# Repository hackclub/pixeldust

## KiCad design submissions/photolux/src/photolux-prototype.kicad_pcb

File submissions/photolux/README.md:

# photolux
created by: Gabriel Tsui [gbtsui] (slack id: U082VP0QX46)

[wokwi](https://wokwi.com/projects/428224523908486145)

I made a simple audio visualizer that takes input from a mono audio jack and flashes colors. It's pretty cool!

## BOM
<!-- Example: -->

| Comment               | Footprint                                               | Quantity | LCSC     | Cost     |
|------------------------|---------------------------------------------------------|----------|----------|----------|
| 100K resistor          | R_0805_2012Metric_Pad1.20x1.40mm_HandSolder              | 2        | C96346   |          |
| Surface mounted Neopixel | LED_SK6812MINI_PLCC4_3.5x3.5mm_P1.75mm                  | 12       |          |          |
| 4.7nF cap              | C_0805_2012Metric_Pad1.18x1.45mm_HandSolder              | 4        | C98192   |          |
| XIAO-RP2040-DIP        | XIAO-RP2040-DIP                                          | 1        |          |          |
| 100uF cap              | C_0805_2012Metric_Pad1.18x1.45mm_HandSolder              | 2        | C141660  |          |
| STX-3000 Audio Jack    | Jack_3.5mm_CUI_SJ-3523-SMT_Horizontal                    | 1        |          |          |
| 10K resistor           | R_0805_2012Metric_Pad1.20x1.40mm_HandSolder              | 2        | C84376   |          |
| 100Ω resistor          | R_0805_2012Metric_Pad1.20x1.40mm_HandSolder              | 1        | C105577  |          |
| 1uF decoupling cap     | C_0805_2012Metric_Pad1.18x1.45mm_HandSolder              | 1        | C28323   |          |
| Surge Protection Chip  | SOT-665                                                 | 1        | C552518  |          |
| 1.5nF cap              | C_0805_2012Metric_Pad1.18x1.45mm_HandSolder              | 1        | C541572  |          |

Design was honestly really hard. Originally I wanted to do baremetal but then i realized how difficult that would be to route and debug. So eventually I switched to my current design and finished it in like 5 hours. I then proceeded to forget about this for 3 weeks before submitting it properly.

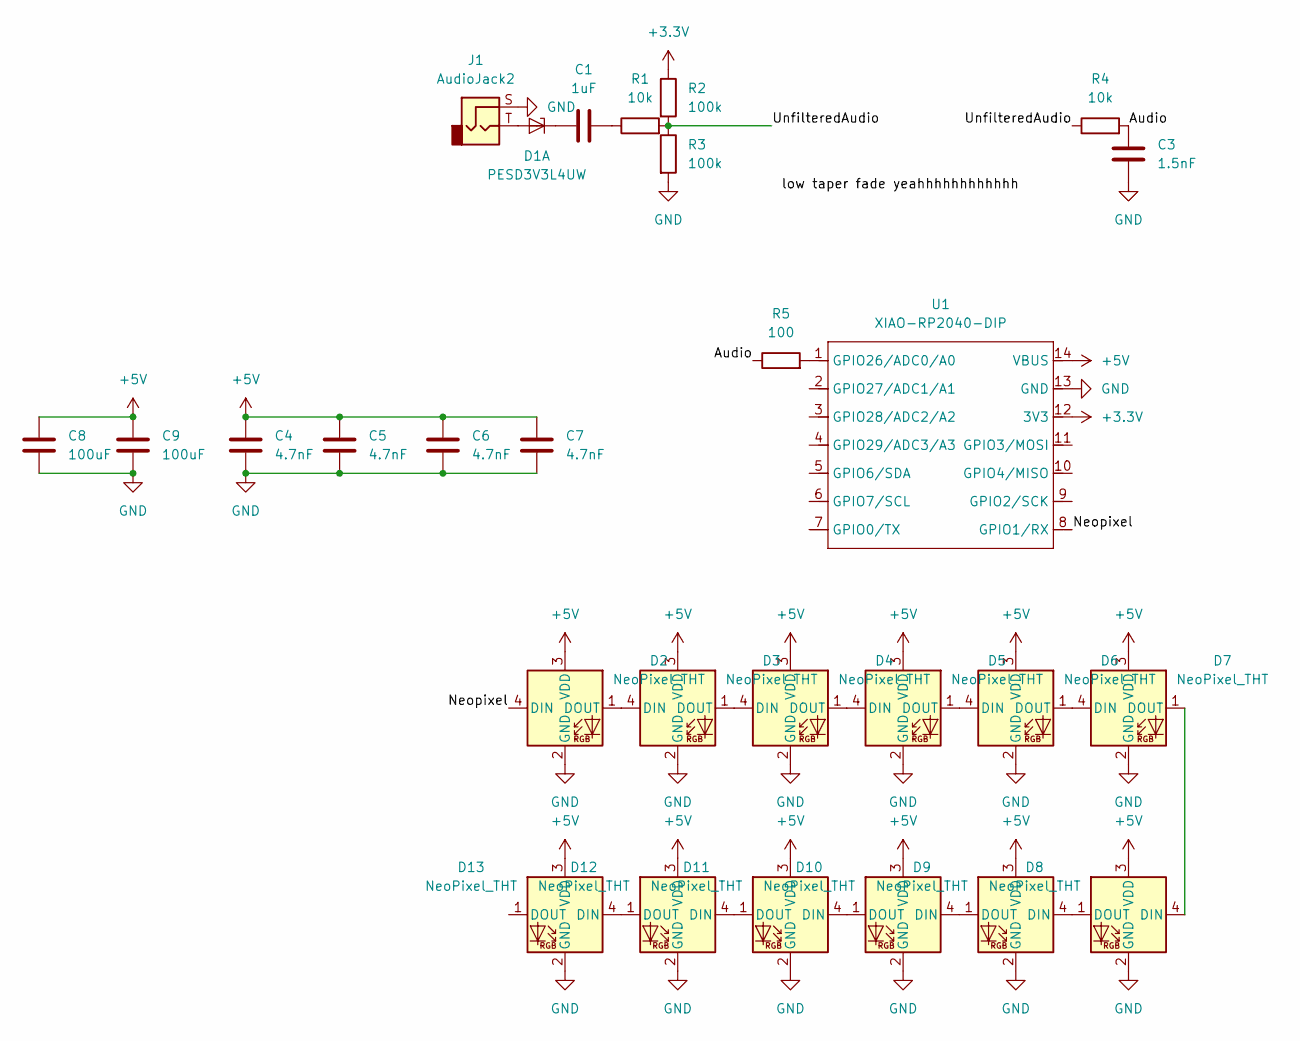
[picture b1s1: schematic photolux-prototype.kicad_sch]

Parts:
C1: 1uF; C_0805_2012Metric_Pad1.18x1.45mm_HandSolder
C3: 1.5nF; C_0805_2012Metric_Pad1.18x1.45mm_HandSolder
C4, C5, C6, C7: 4.7nF; C_0805_2012Metric_Pad1.18x1.45mm_HandSolder
C8, C9: 100uF; C_0805_2012Metric_Pad1.18x1.45mm_HandSolder
D1: PESD3V3L4UW; SOT-665
D2, D3, D4, D5, D6, D7, D8, D9, D10, D11, D12, D13: NeoPixel_THT; LED_SK6812MINI_PLCC4_3.5x3.5mm_P1.75mm
J1: AudioJack2; Jack_3.5mm_CUI_SJ-3523-SMT_Horizontal
R1, R4: 10k; R_0805_2012Metric_Pad1.20x1.40mm_HandSolder
R2, R3: 100k; R_0805_2012Metric_Pad1.20x1.40mm_HandSolder
R5: 100; R_0805_2012Metric_Pad1.20x1.40mm_HandSolder
U1: XIAO-RP2040-DIP

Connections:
+3.3V: R2.1, U1.12 (3V3)
+5V: C4.1, C5.1, C6.1, C7.1, C8.1, C9.1, D2.3 (VDD), D3.3 (VDD), D4.3 (VDD), D5.3 (VDD), D6.3 (VDD), D7.3 (VDD), D8.3 (VDD), D9.3 (VDD), D10.3 (VDD), D11.3 (VDD), D12.3 (VDD), D13.3 (VDD), U1.14 (VBUS)
/Audio: C3.1, R4.2, R5.1
/Neopixel: D2.4 (DIN), U1.8 (GPIO1/RX)
/UnfilteredAudio: R1.2, R2.2, R3.1, R4.1
GND: C3.2, C4.2, C5.2, C6.2, C7.2, C8.2, C9.2, D2.2 (GND), D3.2 (GND), D4.2 (GND), D5.2 (GND), D6.2 (GND), D7.2 (GND), D8.2 (GND), D9.2 (GND), D10.2 (GND), D11.2 (GND), D12.2 (GND), D13.2 (GND), J1.S, R3.2, U1.13 (GND)
unnamed: C1.2, R1.1
unnamed: D1.2 (A), J1.T
unnamed: C1.1, D1.1 (K1)
unnamed: D2.1 (DOUT), D3.4 (DIN)
unnamed: D3.1 (DOUT), D4.4 (DIN)
unnamed: D4.1 (DOUT), D5.4 (DIN)
unnamed: D5.1 (DOUT), D6.4 (DIN)
unnamed: D6.1 (DOUT), D7.4 (DIN)
unnamed: D7.1 (DOUT), D8.4 (DIN)
unnamed: D8.1 (DOUT), D9.4 (DIN)
unnamed: D9.1 (DOUT), D10.4 (DIN)
unnamed: D10.1 (DOUT), D11.4 (DIN)
unnamed: D11.1 (DOUT), D12.4 (DIN)
unnamed: D12.1 (DOUT), D13.4 (DIN)
unnamed: R5.2, U1.1 (GPIO26/ADC0/A0)

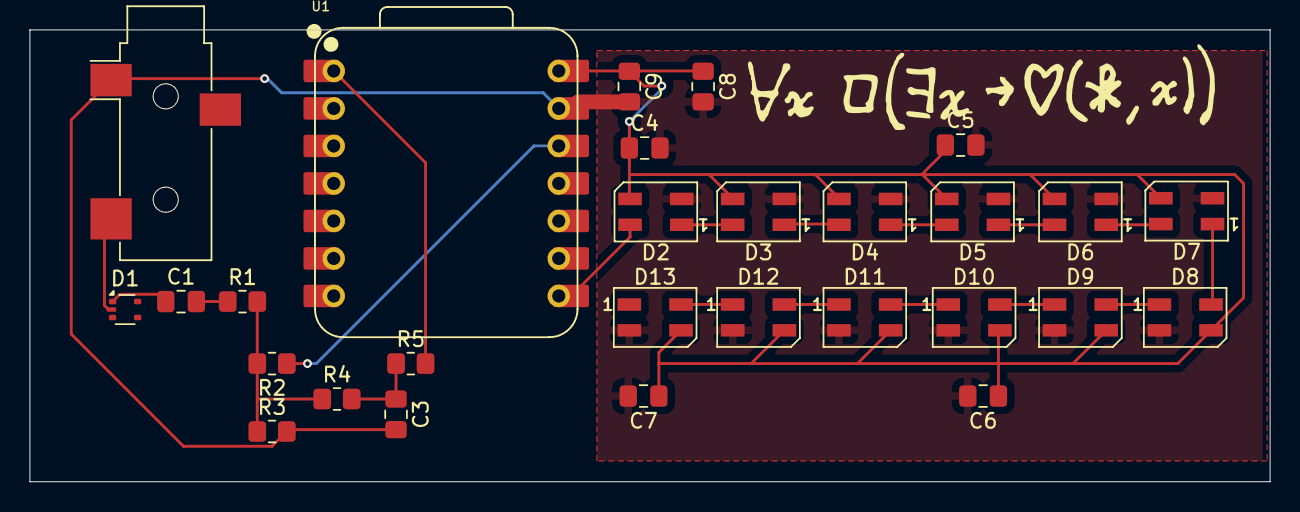
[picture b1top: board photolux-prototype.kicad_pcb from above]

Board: 2 copper layers, 84.0 x 30.6 mm, 28 parts (0 on the bottom side), 21 nets.

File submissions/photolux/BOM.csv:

Id;Designator;Footprint;Quantity;Designation;LCSC;Comments
1;R2,R3;R_0805_2012Metric_Pad1.20x1.40mm_HandSolder;2;100k;C96346;100K resistor
2;D6,D10,D7,D8,D11,D9,D13,D2,D5,D4,D3,D12;LED_SK6812MINI_PLCC4_3.5x3.5mm_P1.75mm;12;NeoPixel_THT;Surface mounted Neopixel;
3;C5,C6,C7,C4;C_0805_2012Metric_Pad1.18x1.45mm_HandSolder;4;4.7nF;C98192;4.7nF cap
4;U1;XIAO-RP2040-DIP;1;XIAO-RP2040-DIP;;
5;C9,C8;C_0805_2012Metric_Pad1.18x1.45mm_HandSolder;2;100uF;C141660;100uF cap
6;J1;Jack_3.5mm_CUI_SJ-3523-SMT_Horizontal;1;AudioJack2;;STX-3000 Audio Jack
7;R4,R1;R_0805_2012Metric_Pad1.20x1.40mm_HandSolder;2;10k;C84376;10K resistor
8;R5;R_0805_2012Metric_Pad1.20x1.40mm_HandSolder;1;100;C105577;100Ohm Resistor
9;C1;C_0805_2012Metric_Pad1.18x1.45mm_HandSolder;1;1uF;C28323;Decoupling Cap
10;D1;SOT-665;1;PESD3V3L4UW;C552518;Surge Protection Chip
11;C3;C_0805_2012Metric_Pad1.18x1.45mm_HandSolder;1;1.5nF;C541572;

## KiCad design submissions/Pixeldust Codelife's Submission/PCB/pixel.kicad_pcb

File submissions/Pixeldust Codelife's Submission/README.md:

name: "Delroy Prithvi Crasto"

slack_id: "U07V5RDRSL8"

github_handle: "@Programer6"

tutorial: [https://pixeldust.hackclub.com/guidelines](https://pixeldust.hackclub.com/guidelines)

wokwi: [https://wokwi.com/projects/430030406209979393](https://wokwi.com/projects/430030406209979393)  

# 10 * 10 Audio visualizer 

Wokwi link: [https://wokwi.com/projects/430030406209979393](https://wokwi.com/projects/430030406209979393)

I would like to solder the PCB myself (as 100 leds in total) and I don't have soldering iron, so I would like to have one.

Describe your board in 2-3 sentences. What are you making? What will it do? 
This board is an audio-reactive LED matrix: a 10x10 array of WS2812B LEDs controlled by an XIAO ESP32-S3. It listens to audio using an ICS-43434 microphone, processes the audio signal with the ESP32-S3, and applies the results to generate light animations on the LED matrix that are dynamically reactive to the audio to produce an eye-grabbing experience. A push button provides a method of user input.

Schematic and PCB images:

A simplified BOM table

| Component                      | Designator(s) | Footprint                                        | Quantity | LCSC Part # | Cost (USD)                           | Notes                                 |
| ------------------------------ | ------------- | ------------------------------------------------ | -------- | ----------- | ------------------------------------ | ------------------------------------- |
| WS2812B LED                    | D1–D100       | SMD5050 (5.0 × 5.0 mm)                           | 100      | C114586     | \$0.0651 each ([LCSC][1], [LCSC][2]) | 50+ price tier; 100 pcs order         |
| XIAO ESP32‑S3                  | U2            | test\:XIAO-ESP32S3-DIP                           | 1        | C20467913   | \$8.2231 ([LCSC][3])                 | 1 pc price                            |
| ICS‑43434 Microphone           | MK1           | Sensor\_Audio\:InvenSense\_ICS-43434‑6\_3.5x2.65 | 1        | —           | \$3.12 each ([DigiKey][4])           | DigiKey pricing for 1 pc              |
| 0.1 µF Capacitor (0603)        | C2            | C\_0603\_1608Metric                              | 1        | C6136995    | \$0.034 ([LCSC][5])                  | Venkel X7R MLCC, 25 V                 |
| 10 kΩ Resistor (0603)          | R1–R3         | R\_0603\_1608Metric                              | 3        | C2889392    | — (not in stock) ([LCSC][6])         | VO 100 mW thick‑film; no price listed |
| Push Button (Cherry MX)        | SW1           | SW\_Cherry\_MX\_1.00u\_PCB                       | 1        | C5687012    | \$1.632 ([LCSC][7])                  | 1+ price tier; out of stock           |
| AMS1117‑3.3 V Regulator        | U1            | SOT‑223‑3                                        | 1        | C6186       | \$0.183 ([LCSC][8])                  | 5+ price tier                         |
| 1000 µF Electrolytic Capacitor | C1            | SMD, D = 10 mm × L = 10.2 mm                     | 1        | C3359       | \$0.1061 ([LCSC][9])                 | Honor Elec, 16 V,  ±20%               |
| 1×3 Pin Header, Vertical       | J1, J2        | PinHeader\_1x03\_P2.54mm\_Vertical               | 2        | C5116482    | \$0.0239 each ([LCSC][10])           | ZHOURI 2.54‑1\*3, 3 pins              |
| Barrel Jack (Würth)            | J3            | Barrel\_Jack\_Switch\_Pin3Ring                   | 1        | —           | — (not on LCSC)                      | Part 694106301002; see Mouser/LCSC†   |
| SMD Indicator LED              | LED           | LED\_SMD\:Generic                                | 1        | —           | — (user‑defined)                     | Status indicator                      |

[1]: https://www.lcsc.com/product-detail/Light-Emitting-Diodes-LED_Worldsemi-WS2812B-B-W_C114586.html "WS2812B-B/W | Worldsemi | Price | In Stock | LCSC Electronics"
[2]: https://www.lcsc.com/product-detail/Light-Emitting-Diodes-LED_5050-RGBIntegrated-Light-4Pin_C114586.html "WS2812B-B/W | Worldsemi | Price | In Stock | LCSC Electronics"
[3]: https://www.lcsc.com/product-detail/Bluetooth-Modules_Seeed-113991114_C20467913.html "113991114 Seeed IoT/Communication Modules | Bluetooth ... - LCSC"
[4]: https://www.digikey.com/en/products/detail/tdk-invensense/ICS-43434/6140298 "ICS-43434 TDK InvenSense | Audio Products - DigiKey"
[5]: https://www.lcsc.com/datasheet/lcsc_datasheet_2411272212_Venkel-C0603X7R250-104JNE-CT_C6136995.pdf "Venkel C0603X7R250-104JNE-CT Datasheet - LCSC"
[6]: https://www.lcsc.com/product-detail/Chip-Resistor-Surface-Mount_VO_C2889392.html "0603 ±5% 10K | VO | Price | In Stock | LCSC Electronics"
[7]: https://www.lcsc.com/product-detail/Mechanical-Keyboard-Shaft_CHERRY-MX1A-11NN_C5687012.html "cherry mx1a-11nn - Mechanical Keyboard Shaft - LCSC"
[8]: https://www.lcsc.com/product-detail/Linear-Voltage-Regulators-LDO_Advanced-Monolithic-Systems-AMS1117-3-3_C6186.html "AMS1117-3.3 | Advanced Monolithic Systems | Price | In Stock - LCSC"
[9]: https://www.lcsc.com/product-detail/Aluminum-Electrolytic-Capacitors-SMD_1000uF-16V_C3359.html "RVT1C102M1010 Honor Elec Capacitors | 1000uF 16V ±20% SMD ..."
[10]: https://www.lcsc.com/product-detail/Pin-Headers_ZHOURI-2-54-1-3_C5116482.html "2.54-1*3 | ZHOURI | Price | In Stock | LCSC Electronics"

Tell us a little bit about your design process. What were some challenges? What helped?

The project started as a portable audio visualizer powered by the ESP32-S3. I had the most difficult time with the first build because manually routing the traces on the PCB for all the components was difficult. I even struggled to fit in 100 LEDs in the design!  In the middle of the frustation, I almost forgot about the auto-tracer that helped move the process along significantly. Another difficultly I had was getting the connections correct for the ICS-43434 microphone, this was due to amount of components and specific pin requirements in the I2S protocol. I had to trace the wiring out from the datasheet to the pins on the ESP32-S3.

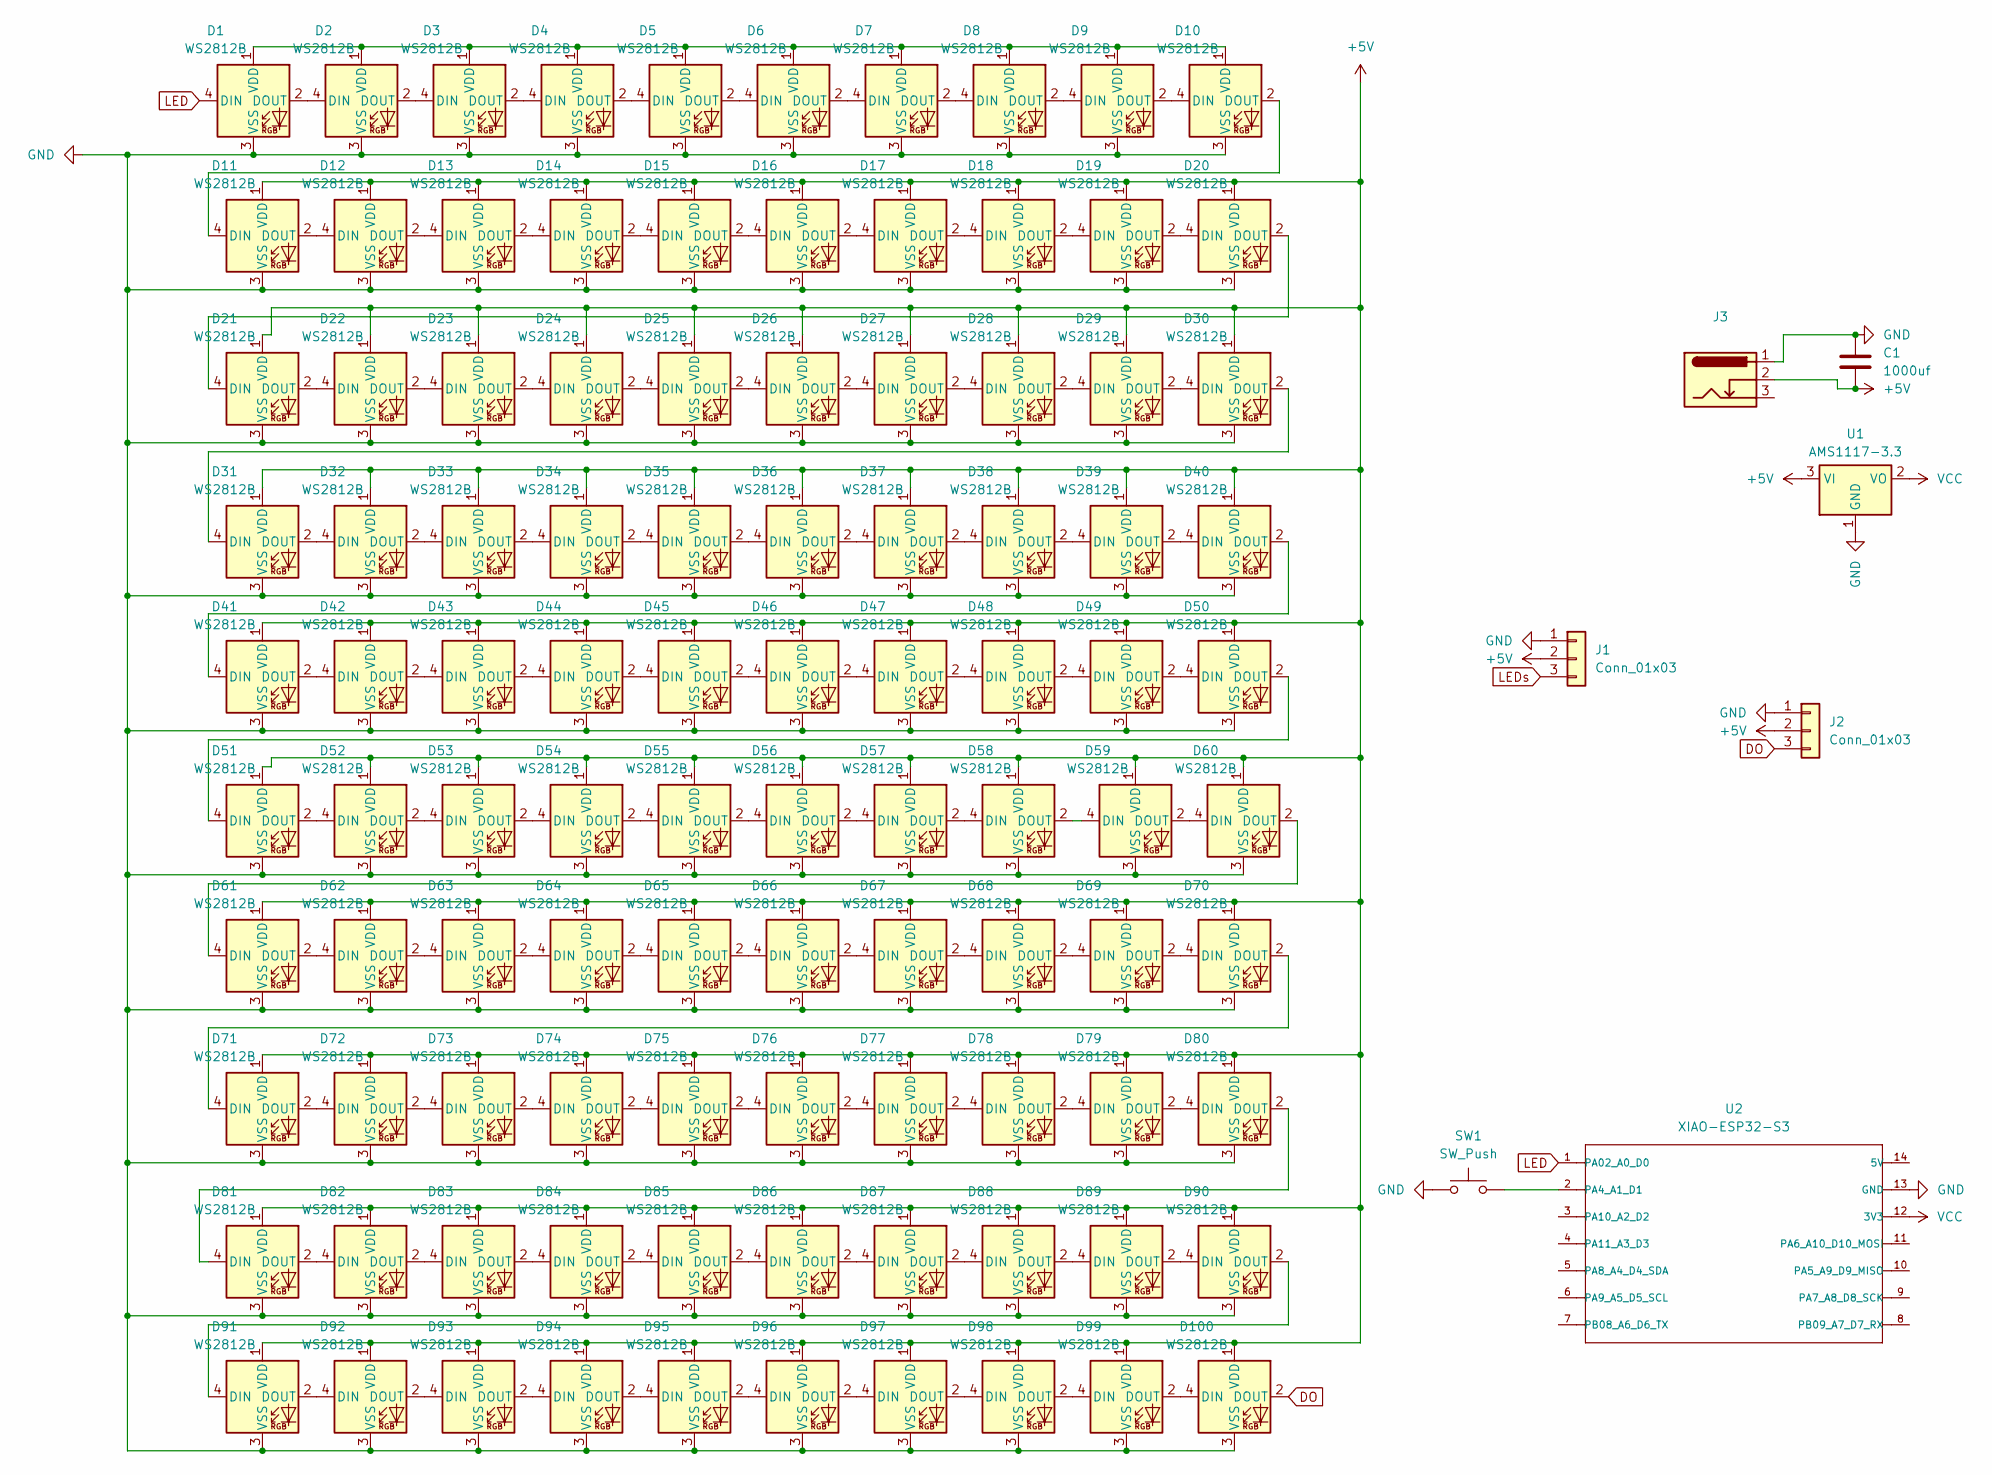
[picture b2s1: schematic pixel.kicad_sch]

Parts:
C1: 1000uf; C_0402_1005Metric
D1, D2, D3, D4, D5, D6, D7, D8, D9, D10, D11, D12, D13, D14, D15, D16, D17, D18, D19, D20, D21, D22, D23, D24, D25, D26, D27, D28, D29, D30, D31, D32, D33, D34, D35, D36, D37, D38, D39, D40, D41, D42, D43, D44, D45, D46, D47, D48, D49, D50, D51, D52, D53, D54, D55, D56, D57, D58, D59, D60, D61, D62, D63, D64, D65, D66, D67, D68, D69, D70, D71, D72, D73, D74, D75, D76, D77, D78, D79, D80, D81, D82, D83, D84, D85, D86, D87, D88, D89, D90, D91, D92, D93, D94, D95, D96, D97, D98, D99, D100: WS2812B; LED_WS2812B_PLCC4_5.0x5.0mm_P3.2mm
J1, J2: Conn_01x03; PinHeader_1x03_P2.54mm_Vertical
J3: Barrel_Jack_Switch_Pin3Ring; BarrelJack_Wuerth_6941xx301002
SW1: SW_Push; SW_Cherry_MX_1.00u_PCB
U1: AMS1117-3.3; SOT-223-3_TabPin2
U2: XIAO-ESP32-S3; XIAO-ESP32S3-DIP

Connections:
+5V: C1.2, D11.1 (VDD), D12.1 (VDD), D13.1 (VDD), D14.1 (VDD), D15.1 (VDD), D16.1 (VDD), D17.1 (VDD), D18.1 (VDD), D19.1 (VDD), D20.1 (VDD), D21.1 (VDD), D22.1 (VDD), D23.1 (VDD), D24.1 (VDD), D25.1 (VDD), D26.1 (VDD), D27.1 (VDD), D28.1 (VDD), D29.1 (VDD), D30.1 (VDD), D31.1 (VDD), D32.1 (VDD), D33.1 (VDD), D34.1 (VDD), D35.1 (VDD), D36.1 (VDD), D37.1 (VDD), D38.1 (VDD), D39.1 (VDD), D40.1 (VDD), D41.1 (VDD), D42.1 (VDD), D43.1 (VDD), D44.1 (VDD), D45.1 (VDD), D46.1 (VDD), D47.1 (VDD), D48.1 (VDD), D49.1 (VDD), D50.1 (VDD), D51.1 (VDD), D52.1 (VDD), D53.1 (VDD), D54.1 (VDD), D55.1 (VDD), D56.1 (VDD), D57.1 (VDD), D58.1 (VDD), D59.1 (VDD), D60.1 (VDD), D61.1 (VDD), D62.1 (VDD), D63.1 (VDD), D64.1 (VDD), D65.1 (VDD), D66.1 (VDD), D67.1 (VDD), D68.1 (VDD), D69.1 (VDD), D70.1 (VDD), D71.1 (VDD), D72.1 (VDD), D73.1 (VDD), D74.1 (VDD), D75.1 (VDD), D76.1 (VDD), D77.1 (VDD), D78.1 (VDD), D79.1 (VDD), D80.1 (VDD), D81.1 (VDD), D82.1 (VDD), D83.1 (VDD), D84.1 (VDD), D85.1 (VDD), D86.1 (VDD), D87.1 (VDD), D88.1 (VDD), D89.1 (VDD), D90.1 (VDD), D91.1 (VDD), D92.1 (VDD), D93.1 (VDD), D94.1 (VDD), D95.1 (VDD), D96.1 (VDD), D97.1 (VDD), D98.1 (VDD), D99.1 (VDD), D100.1 (VDD), J1.2, J2.2, J3.2, U1.3 (VI)
DO: D100.2 (DOUT), J2.3
GND: C1.1, D1.3 (VSS), D2.3 (VSS), D3.3 (VSS), D4.3 (VSS), D5.3 (VSS), D6.3 (VSS), D7.3 (VSS), D8.3 (VSS), D9.3 (VSS), D10.3 (VSS), D11.3 (VSS), D12.3 (VSS), D13.3 (VSS), D14.3 (VSS), D15.3 (VSS), D16.3 (VSS), D17.3 (VSS), D18.3 (VSS), D19.3 (VSS), D20.3 (VSS), D21.3 (VSS), D22.3 (VSS), D23.3 (VSS), D24.3 (VSS), D25.3 (VSS), D26.3 (VSS), D27.3 (VSS), D28.3 (VSS), D29.3 (VSS), D30.3 (VSS), D31.3 (VSS), D32.3 (VSS), D33.3 (VSS), D34.3 (VSS), D35.3 (VSS), D36.3 (VSS), D37.3 (VSS), D38.3 (VSS), D39.3 (VSS), D40.3 (VSS), D41.3 (VSS), D42.3 (VSS), D43.3 (VSS), D44.3 (VSS), D45.3 (VSS), D46.3 (VSS), D47.3 (VSS), D48.3 (VSS), D49.3 (VSS), D50.3 (VSS), D51.3 (VSS), D52.3 (VSS), D53.3 (VSS), D54.3 (VSS), D55.3 (VSS), D56.3 (VSS), D57.3 (VSS), D58.3 (VSS), D59.3 (VSS), D60.3 (VSS), D61.3 (VSS), D62.3 (VSS), D63.3 (VSS), D64.3 (VSS), D65.3 (VSS), D66.3 (VSS), D67.3 (VSS), D68.3 (VSS), D69.3 (VSS), D70.3 (VSS), D71.3 (VSS), D72.3 (VSS), D73.3 (VSS), D74.3 (VSS), D75.3 (VSS), D76.3 (VSS), D77.3 (VSS), D78.3 (VSS), D79.3 (VSS), D80.3 (VSS), D81.3 (VSS), D82.3 (VSS), D83.3 (VSS), D84.3 (VSS), D85.3 (VSS), D86.3 (VSS), D87.3 (VSS), D88.3 (VSS), D89.3 (VSS), D90.3 (VSS), D91.3 (VSS), D92.3 (VSS), D93.3 (VSS), D94.3 (VSS), D95.3 (VSS), D96.3 (VSS), D97.3 (VSS), D98.3 (VSS), D99.3 (VSS), D100.3 (VSS), J1.1, J2.1, J3.1, SW1.1, U1.1 (GND), U2.13 (GND); also elsewhere on the board
LED: D1.4 (DIN), U2.1 (PA02_A0_D0)
LEDs: J1.3
unnamed: D1.2 (DOUT), D2.4 (DIN)
unnamed: D1.1 (VDD), D2.1 (VDD), D3.1 (VDD), D4.1 (VDD), D5.1 (VDD), D6.1 (VDD), D7.1 (VDD), D8.1 (VDD), D9.1 (VDD), D10.1 (VDD)
unnamed: D2.2 (DOUT), D3.4 (DIN)
unnamed: D3.2 (DOUT), D4.4 (DIN)
unnamed: D4.2 (DOUT), D5.4 (DIN)
unnamed: D5.2 (DOUT), D6.4 (DIN)
unnamed: D6.2 (DOUT), D7.4 (DIN)
unnamed: D7.2 (DOUT), D8.4 (DIN)
unnamed: D8.2 (DOUT), D9.4 (DIN)
unnamed: D9.2 (DOUT), D10.4 (DIN)
unnamed: D10.2 (DOUT), D11.4 (DIN)
unnamed: D11.2 (DOUT), D12.4 (DIN)
unnamed: D12.2 (DOUT), D13.4 (DIN)
unnamed: D13.2 (DOUT), D14.4 (DIN)
unnamed: D14.2 (DOUT), D15.4 (DIN)
unnamed: D15.2 (DOUT), D16.4 (DIN)
unnamed: D16.2 (DOUT), D17.4 (DIN)
unnamed: D17.2 (DOUT), D18.4 (DIN)
unnamed: D18.2 (DOUT), D19.4 (DIN)
unnamed: D19.2 (DOUT), D20.4 (DIN)
unnamed: D20.2 (DOUT), D21.4 (DIN)
unnamed: D21.2 (DOUT), D22.4 (DIN)
unnamed: D22.2 (DOUT), D23.4 (DIN)
unnamed: D23.2 (DOUT), D24.4 (DIN)
unnamed: D24.2 (DOUT), D25.4 (DIN)
unnamed: D25.2 (DOUT), D26.4 (DIN)
unnamed: D26.2 (DOUT), D27.4 (DIN)
unnamed: D27.2 (DOUT), D28.4 (DIN)
unnamed: D28.2 (DOUT), D29.4 (DIN)
unnamed: D29.2 (DOUT), D30.4 (DIN)
unnamed: D30.2 (DOUT), D31.4 (DIN)
unnamed: D31.2 (DOUT), D32.4 (DIN)
unnamed: D32.2 (DOUT), D33.4 (DIN)
unnamed: D33.2 (DOUT), D34.4 (DIN)
unnamed: D34.2 (DOUT), D35.4 (DIN)
unnamed: D35.2 (DOUT), D36.4 (DIN)
unnamed: D36.2 (DOUT), D37.4 (DIN)
unnamed: D37.2 (DOUT), D38.4 (DIN)
unnamed: D38.2 (DOUT), D39.4 (DIN)
unnamed: D39.2 (DOUT), D40.4 (DIN)
unnamed: D40.2 (DOUT), D41.4 (DIN)
unnamed: D41.2 (DOUT), D42.4 (DIN)
unnamed: D42.2 (DOUT), D43.4 (DIN)
unnamed: D43.2 (DOUT), D44.4 (DIN)
unnamed: D44.2 (DOUT), D45.4 (DIN)
unnamed: D45.2 (DOUT), D46.4 (DIN)
unnamed: D46.2 (DOUT), D47.4 (DIN)
unnamed: D47.2 (DOUT), D48.4 (DIN)
unnamed: D48.2 (DOUT), D49.4 (DIN)
unnamed: D49.2 (DOUT), D50.4 (DIN)
unnamed: D50.2 (DOUT), D51.4 (DIN)
unnamed: D51.2 (DOUT), D52.4 (DIN)
unnamed: D52.2 (DOUT), D53.4 (DIN)
unnamed: D53.2 (DOUT), D54.4 (DIN)
unnamed: D54.2 (DOUT), D55.4 (DIN)
unnamed: D55.2 (DOUT), D56.4 (DIN)
unnamed: D56.2 (DOUT), D57.4 (DIN)
unnamed: D57.2 (DOUT), D58.4 (DIN)
unnamed: D58.2 (DOUT), D59.4 (DIN)
unnamed: D59.2 (DOUT), D60.4 (DIN)
unnamed: D60.2 (DOUT), D61.4 (DIN)
unnamed: D61.2 (DOUT), D62.4 (DIN)
unnamed: D62.2 (DOUT), D63.4 (DIN)
unnamed: D63.2 (DOUT), D64.4 (DIN)
unnamed: D64.2 (DOUT), D65.4 (DIN)
unnamed: D65.2 (DOUT), D66.4 (DIN)
unnamed: D66.2 (DOUT), D67.4 (DIN)
unnamed: D67.2 (DOUT), D68.4 (DIN)
unnamed: D68.2 (DOUT), D69.4 (DIN)
unnamed: D69.2 (DOUT), D70.4 (DIN)
unnamed: D70.2 (DOUT), D71.4 (DIN)
unnamed: D71.2 (DOUT), D72.4 (DIN)
unnamed: D72.2 (DOUT), D73.4 (DIN)
unnamed: D73.2 (DOUT), D74.4 (DIN)
unnamed: D74.2 (DOUT), D75.4 (DIN)
unnamed: D75.2 (DOUT), D76.4 (DIN)
unnamed: D76.2 (DOUT), D77.4 (DIN)
unnamed: D77.2 (DOUT), D78.4 (DIN)
unnamed: D78.2 (DOUT), D79.4 (DIN)
unnamed: D79.2 (DOUT), D80.4 (DIN)
unnamed: D80.2 (DOUT), D81.4 (DIN)
unnamed: D81.2 (DOUT), D82.4 (DIN)
unnamed: D82.2 (DOUT), D83.4 (DIN)
unnamed: D83.2 (DOUT), D84.4 (DIN)
unnamed: D84.2 (DOUT), D85.4 (DIN)
unnamed: D85.2 (DOUT), D86.4 (DIN)
unnamed: D86.2 (DOUT), D87.4 (DIN)
unnamed: D87.2 (DOUT), D88.4 (DIN)
unnamed: D88.2 (DOUT), D89.4 (DIN)
unnamed: D89.2 (DOUT), D90.4 (DIN)
unnamed: D90.2 (DOUT), D91.4 (DIN)
unnamed: D91.2 (DOUT), D92.4 (DIN)
unnamed: D92.2 (DOUT), D93.4 (DIN)
unnamed: D93.2 (DOUT), D94.4 (DIN)
unnamed: D94.2 (DOUT), D95.4 (DIN)
unnamed: D95.2 (DOUT), D96.4 (DIN)
unnamed: D96.2 (DOUT), D97.4 (DIN)
unnamed: D97.2 (DOUT), D98.4 (DIN)
unnamed: D98.2 (DOUT), D99.4 (DIN)
unnamed: D99.2 (DOUT), D100.4 (DIN)
unnamed 105: U2.6 (PA9_A5_D5_SCL); also elsewhere on the board
unnamed 106: U2.5 (PA8_A4_D4_SDA); also elsewhere on the board
unnamed 107: U2.8 (PB09_A7_D7_RX); also elsewhere on the board
unnamed: SW1.2, U2.2 (PA4_A1_D1)
VCC: U1.2 (VO), U2.12 (3V3); also elsewhere on the board

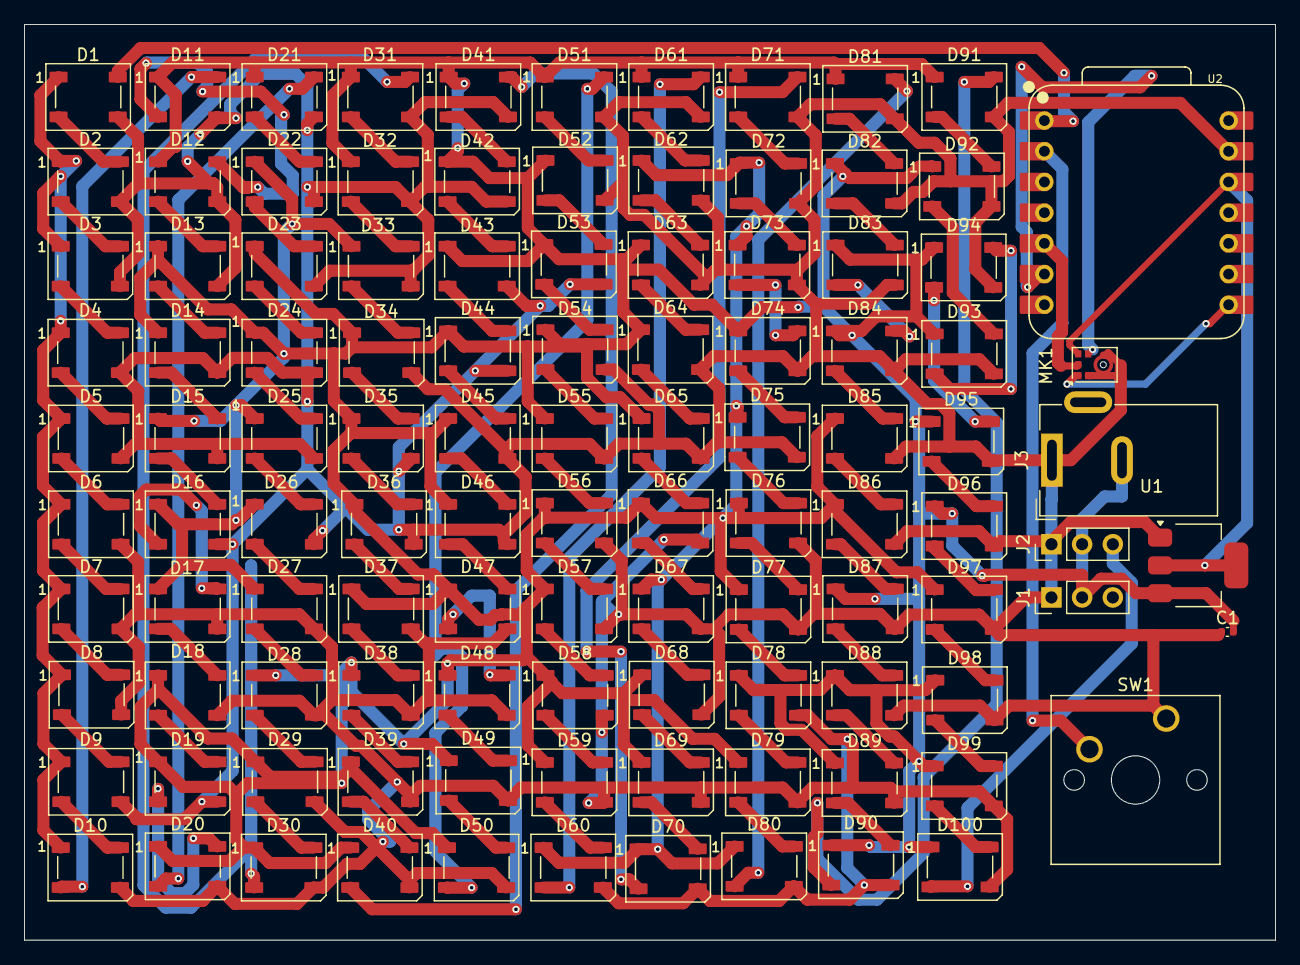
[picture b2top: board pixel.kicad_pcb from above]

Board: 2 copper layers, 103.5 x 75.8 mm, 108 parts (0 on the bottom side), 109 nets.

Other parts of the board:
MK1: ICS-43434; InvenSense_ICS-43434-6_3.5x2.65mm

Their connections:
GND: MK1.2 (LR), MK1.3 (GND); also elsewhere on the board
unnamed 105: MK1.4 (SCK); also elsewhere on the board
unnamed 106: MK1.6 (SD); also elsewhere on the board
unnamed 107: MK1.1 (WS); also elsewhere on the board
VCC: MK1.5 (VDD); also elsewhere on the board
